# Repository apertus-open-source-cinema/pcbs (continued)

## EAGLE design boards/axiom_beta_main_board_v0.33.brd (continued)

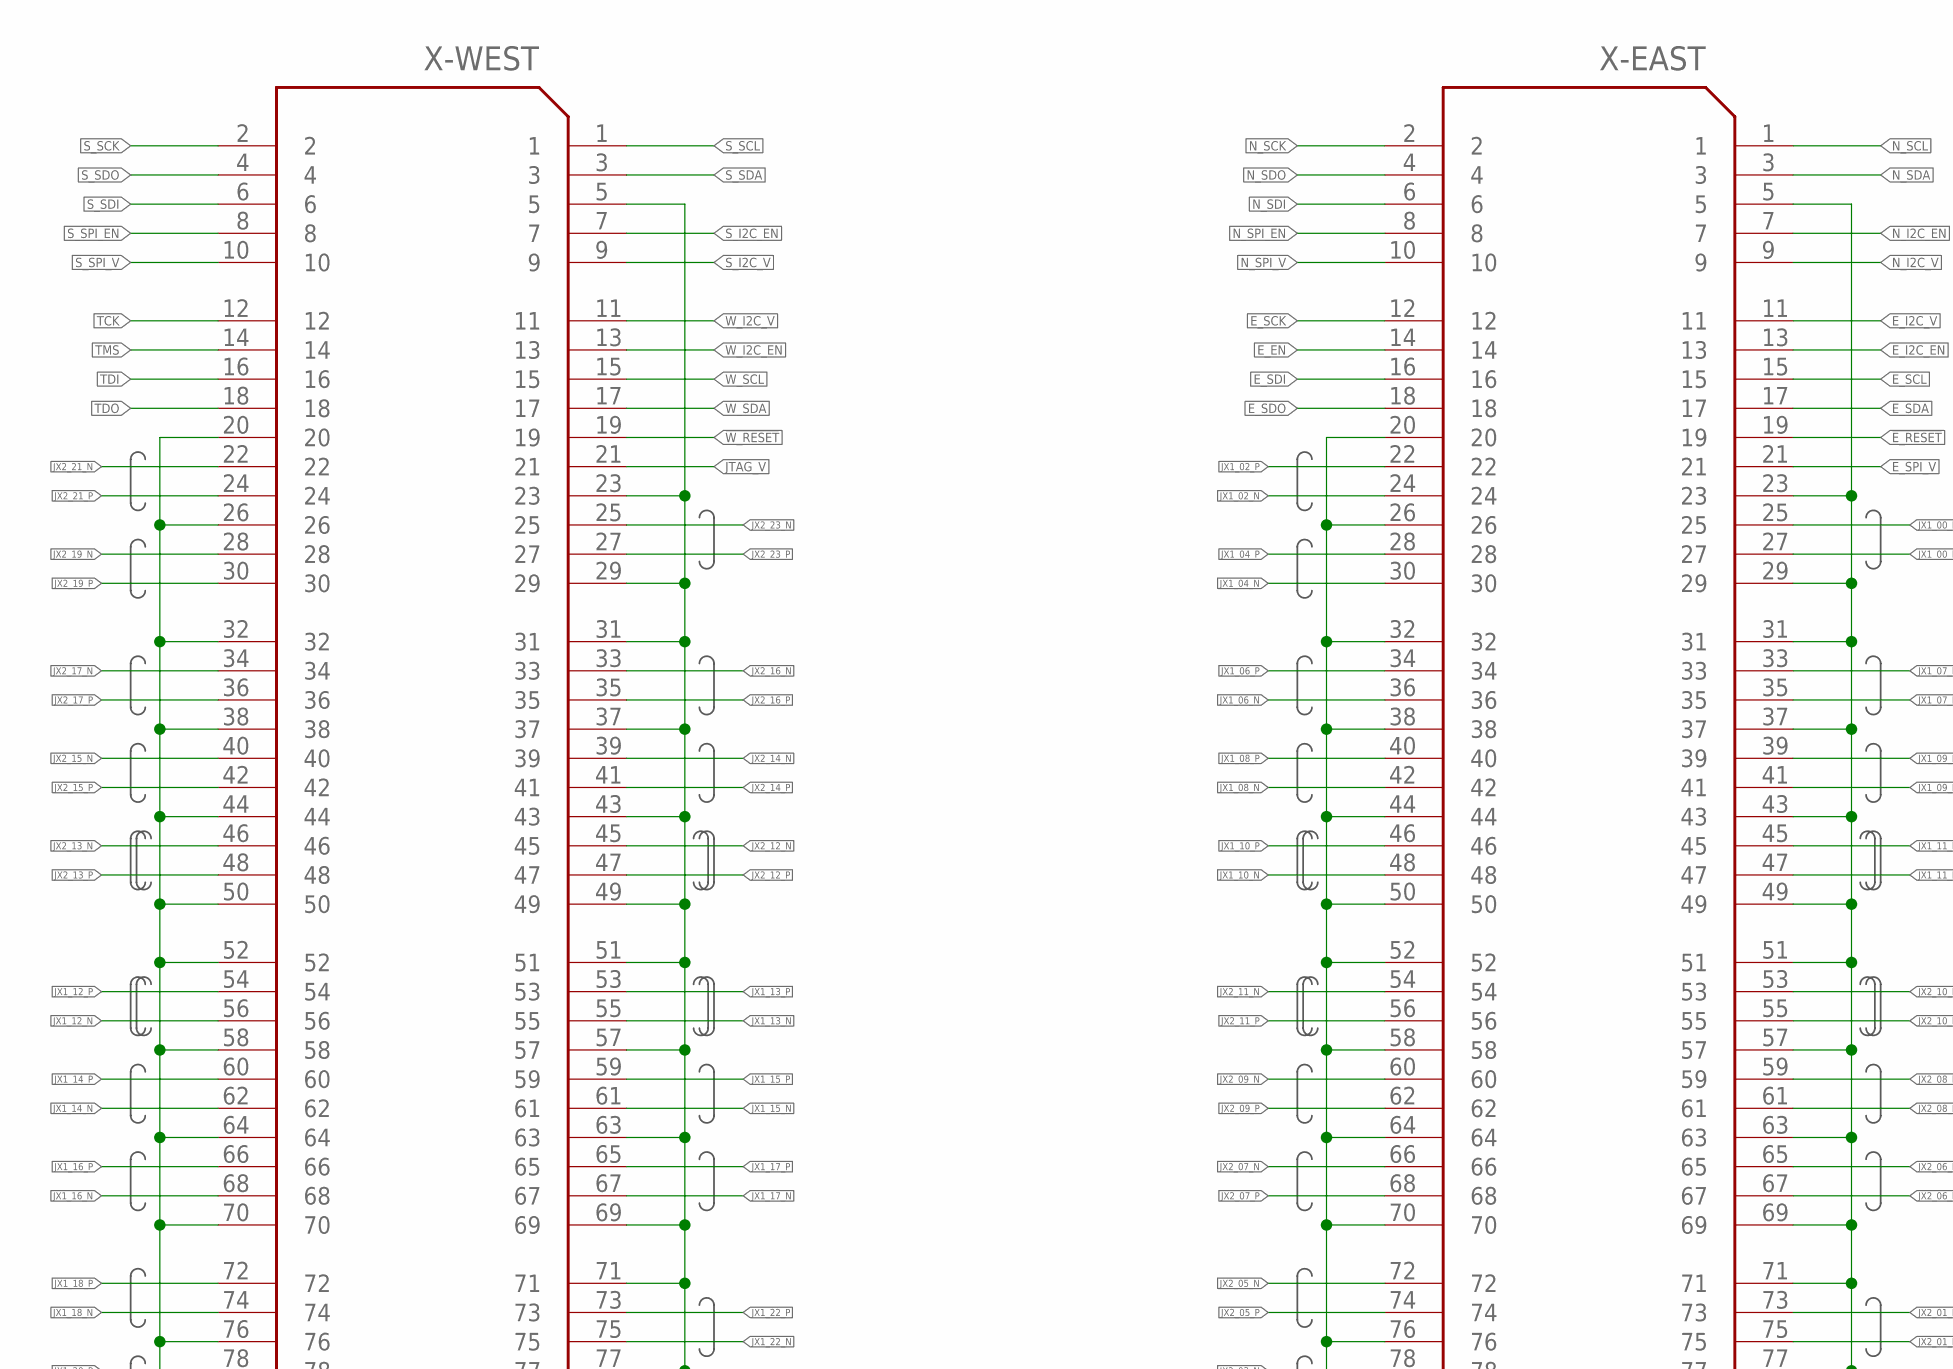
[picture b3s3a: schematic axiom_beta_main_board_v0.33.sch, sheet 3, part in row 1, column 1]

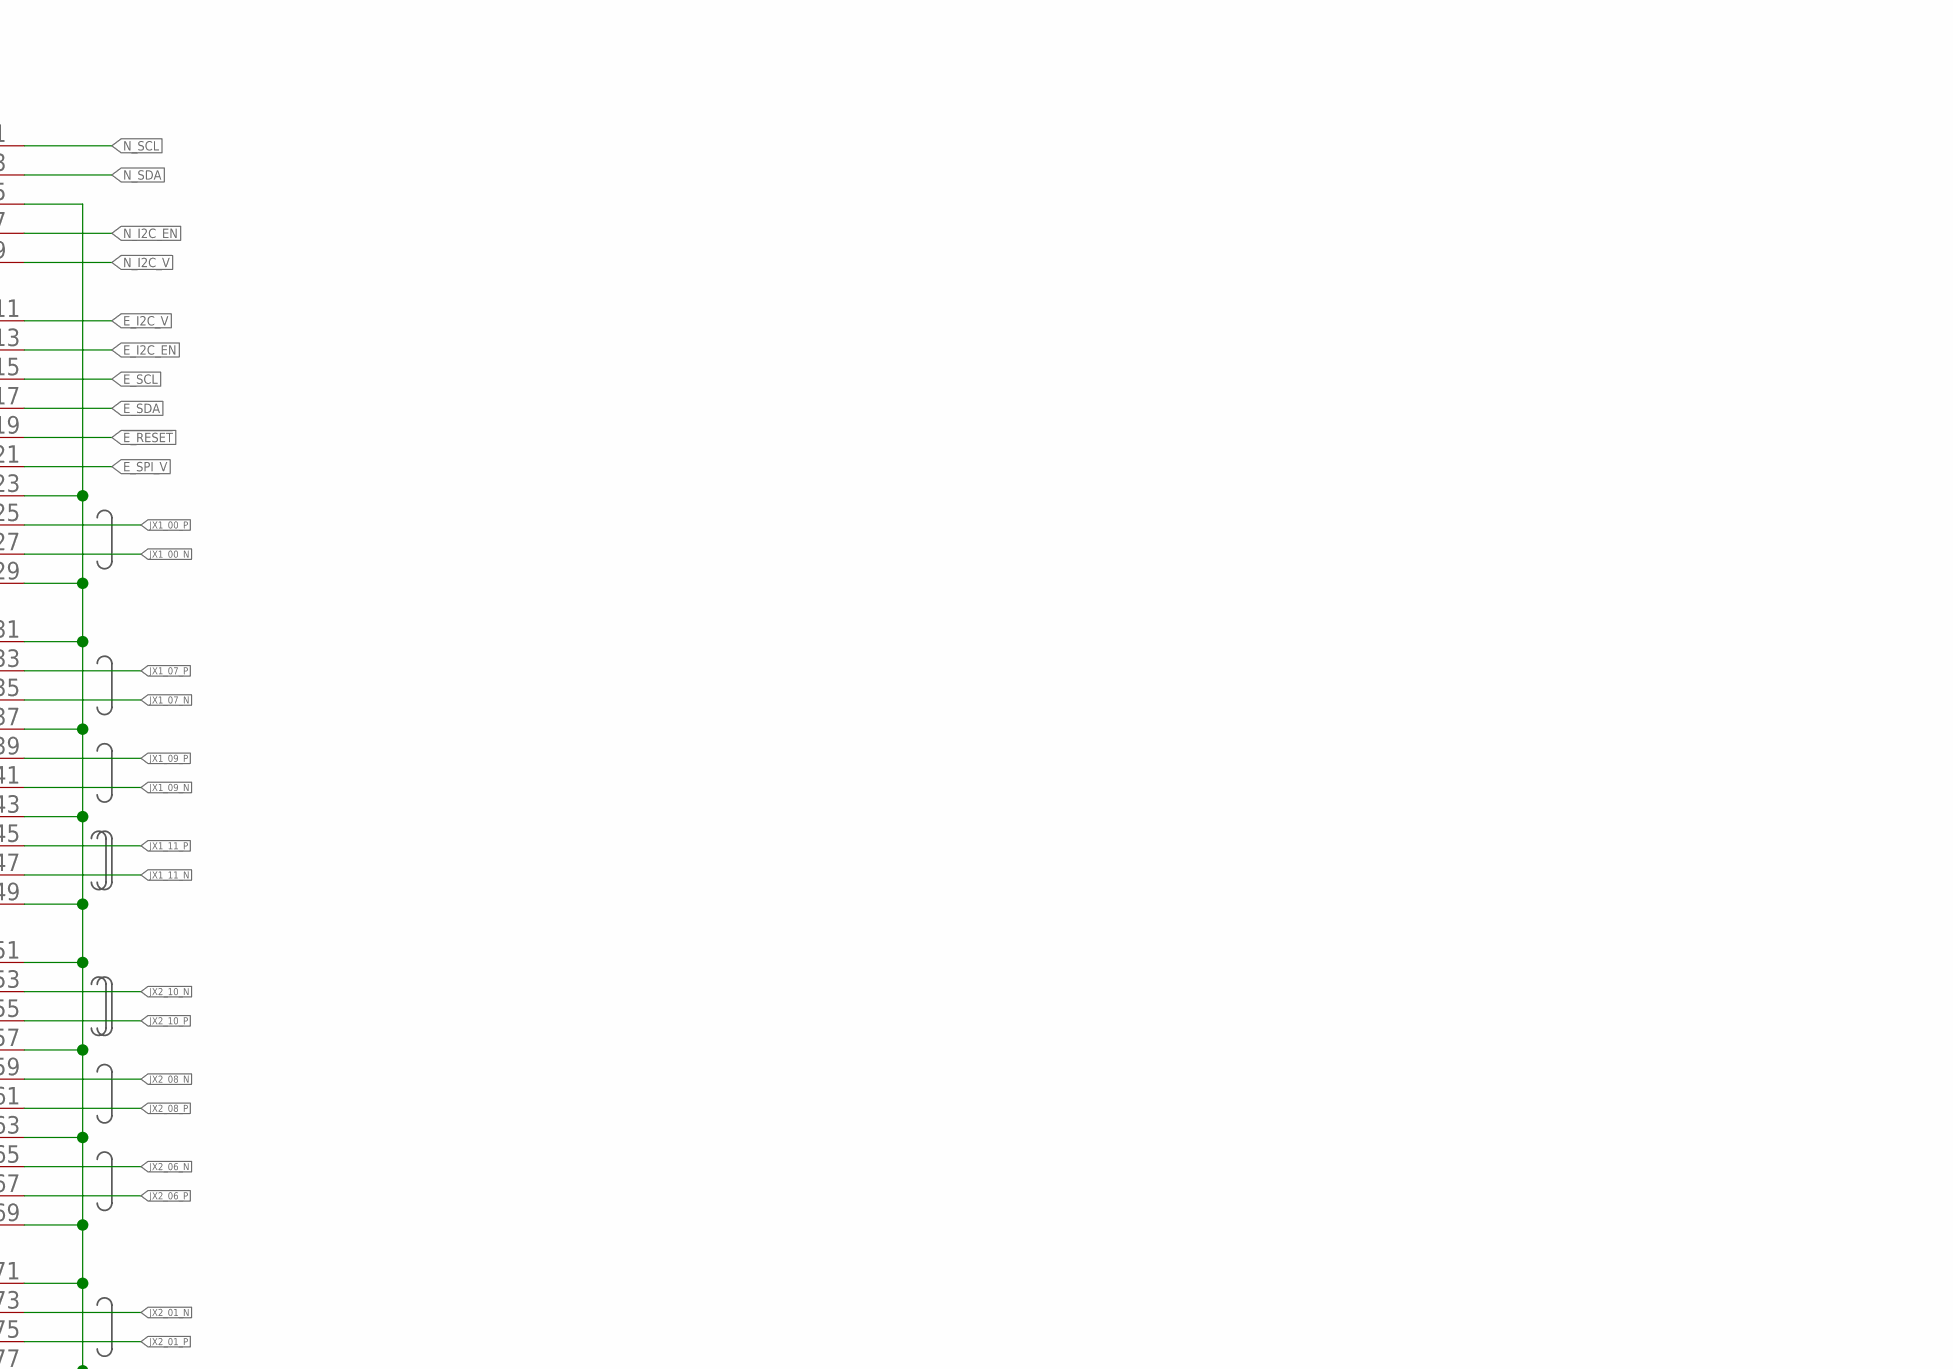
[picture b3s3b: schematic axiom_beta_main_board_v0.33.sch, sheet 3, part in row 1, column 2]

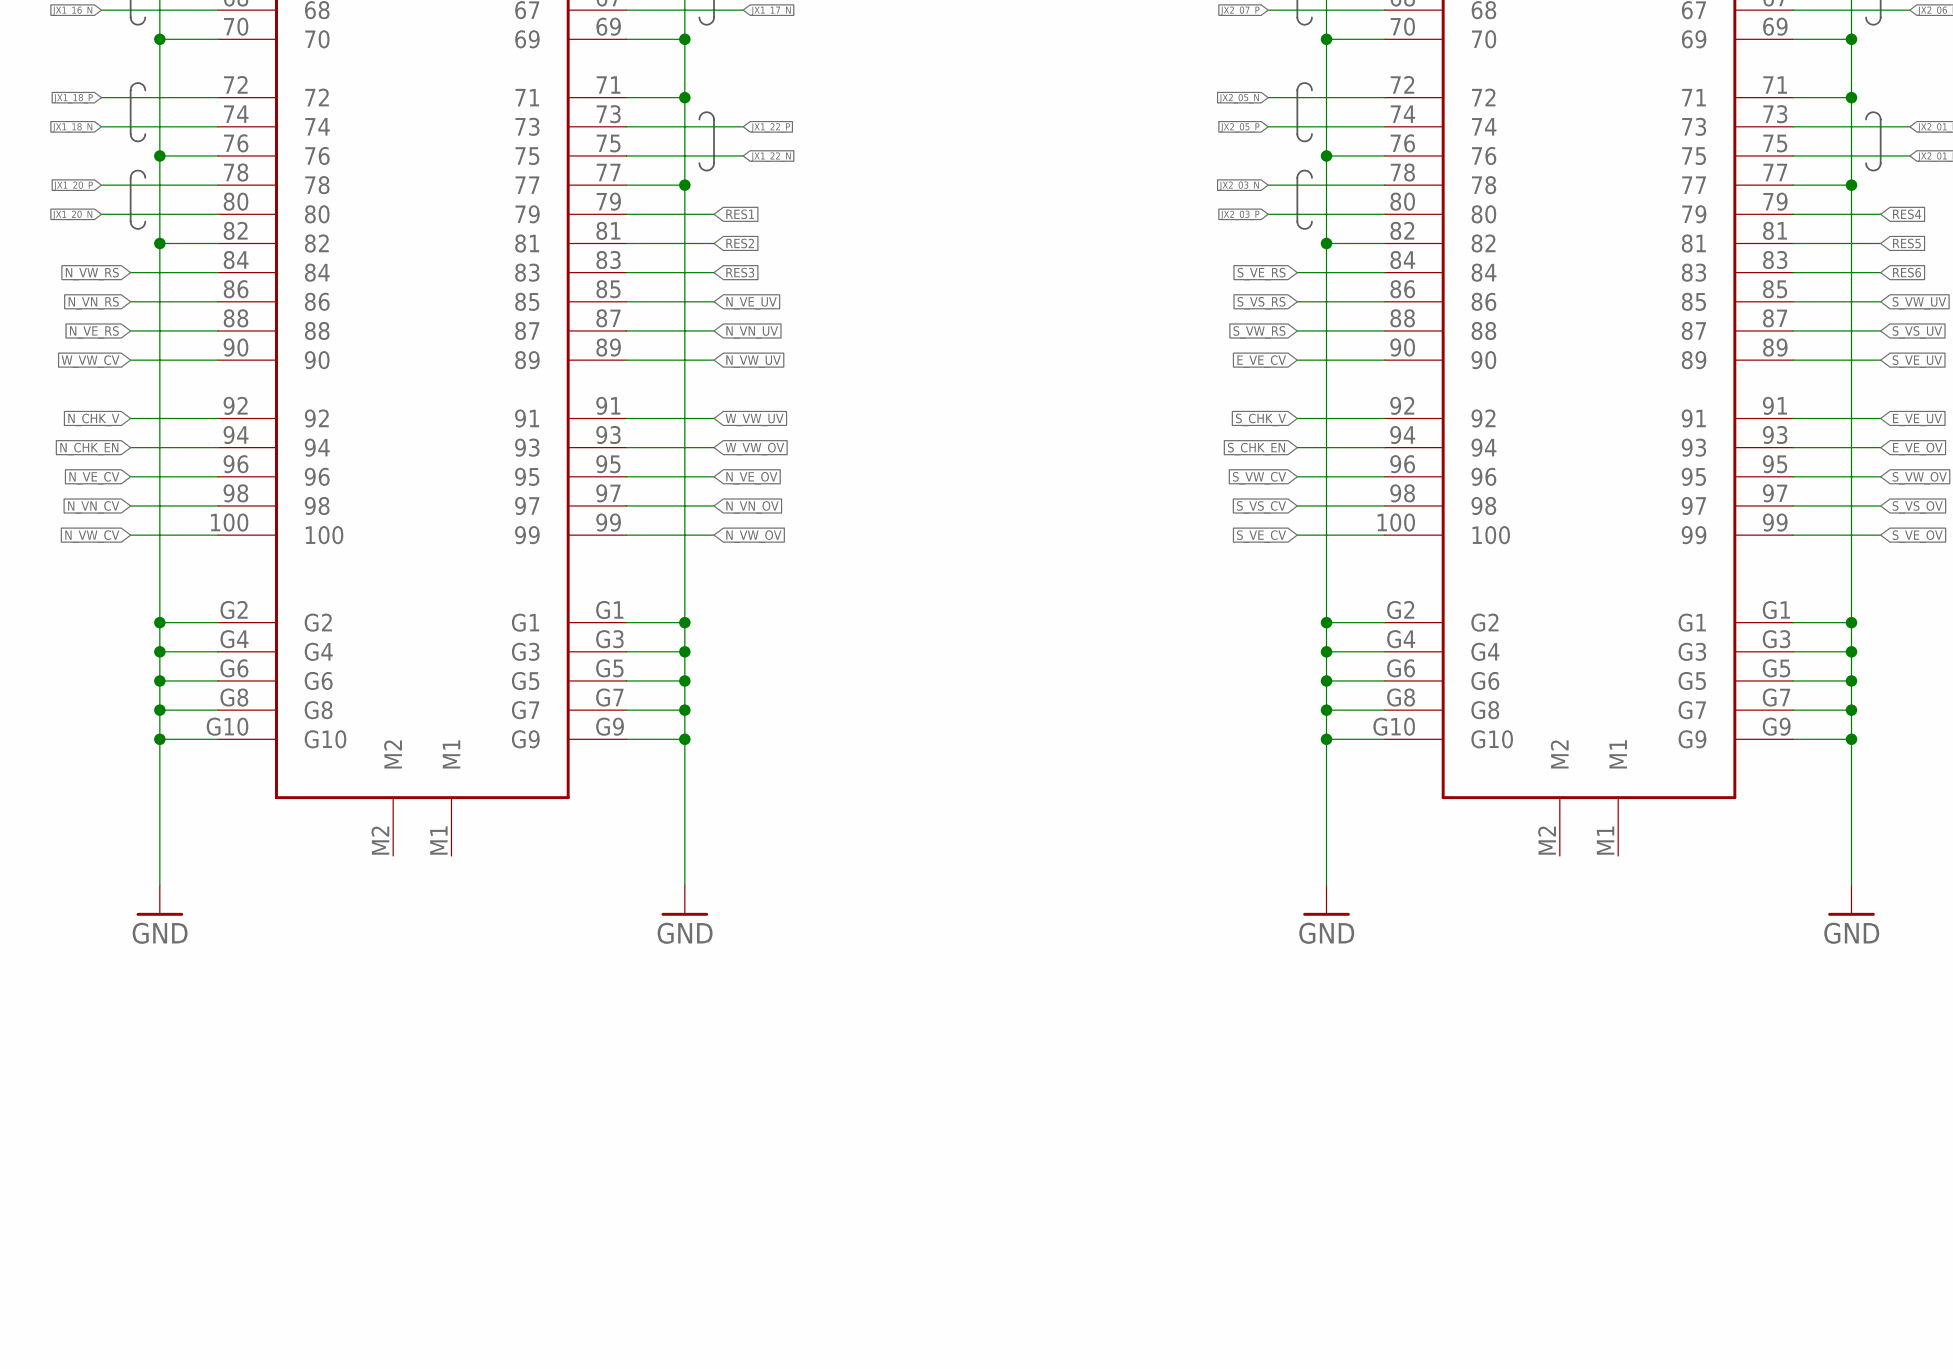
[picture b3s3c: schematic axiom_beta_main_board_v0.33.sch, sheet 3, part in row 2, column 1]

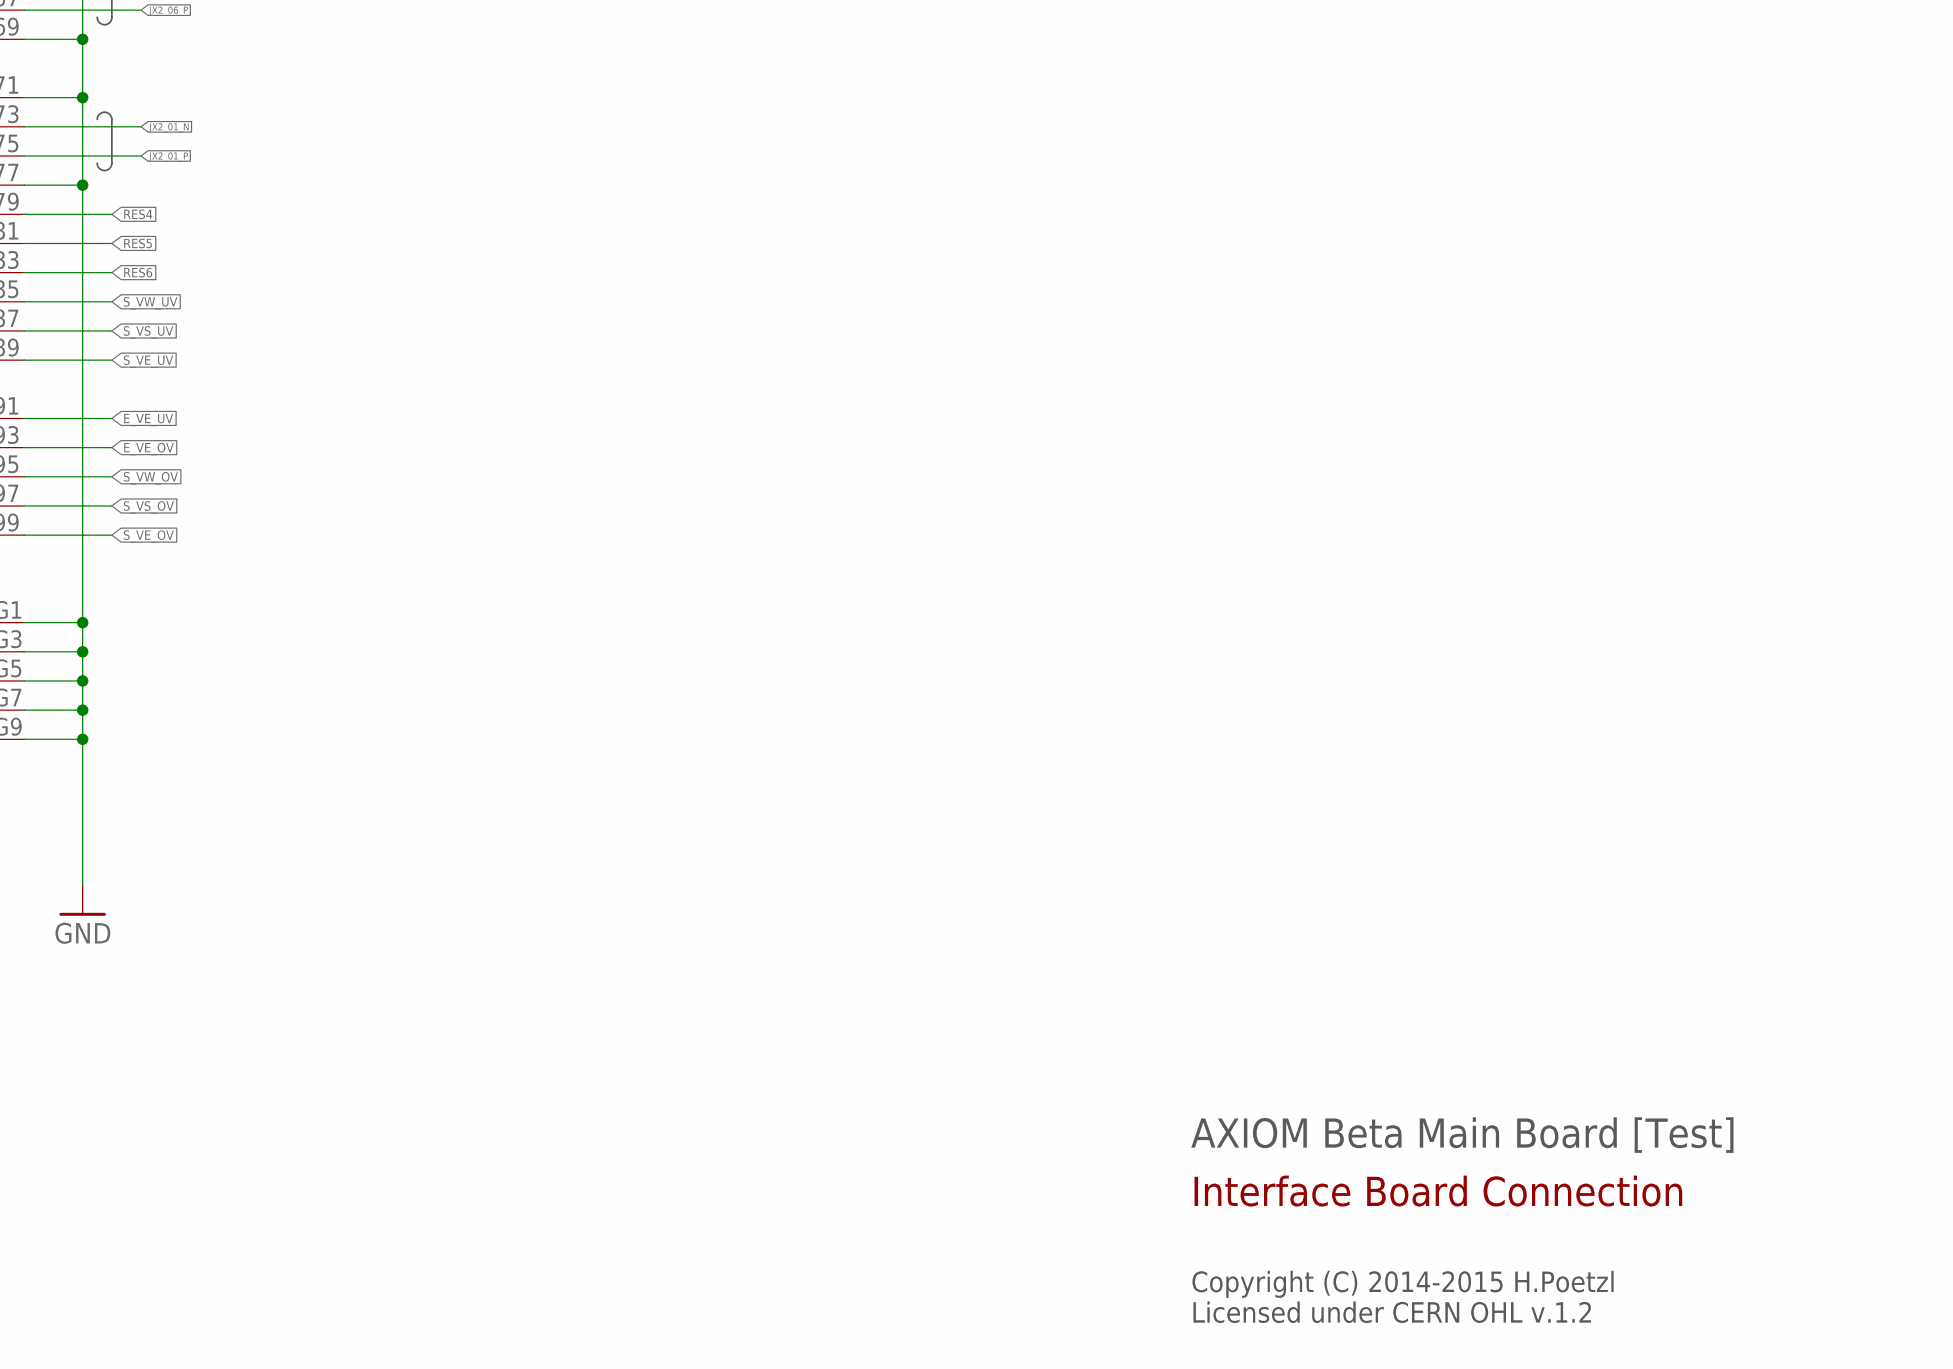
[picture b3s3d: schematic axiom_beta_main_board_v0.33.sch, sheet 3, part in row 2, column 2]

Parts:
X-EAST: FX10-100/10S; FX10A-100S/10
X-WEST: FX10-100/10S; FX10A-100S/10

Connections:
!E_RESET!: X-EAST.19
!W_RESET!: X-WEST.19
E_EN: X-EAST.14; also elsewhere on the board
E_I2C_EN: X-EAST.13
E_I2C_V: X-EAST.11; also elsewhere on the board
E_SCK: X-EAST.12; also elsewhere on the board
E_SCL: X-EAST.15; also elsewhere on the board
E_SDA: X-EAST.17; also elsewhere on the board
E_SDI: X-EAST.16; also elsewhere on the board
E_SDO: X-EAST.18; also elsewhere on the board
E_SPI_V: X-EAST.21; also elsewhere on the board
E_VE_CV: X-EAST.90; also elsewhere on the board
E_VE_OV: X-EAST.93; also elsewhere on the board
E_VE_UV: X-EAST.91; also elsewhere on the board
GND: X-EAST.5, X-EAST.20, X-EAST.23, X-EAST.26, X-EAST.29, X-EAST.31, X-EAST.32, X-EAST.37, X-EAST.38, X-EAST.43, X-EAST.44, X-EAST.49, X-EAST.50, X-EAST.51, X-EAST.52, X-EAST.57, X-EAST.58, X-EAST.63, X-EAST.64, X-EAST.69, X-EAST.70, X-EAST.71, X-EAST.76, X-EAST.77, X-EAST.82, X-EAST.G1, X-EAST.G2, X-EAST.G3, X-EAST.G4, X-EAST.G5, X-EAST.G6, X-EAST.G7, X-EAST.G8, X-EAST.G9, X-EAST.G10, X-WEST.5, X-WEST.20, X-WEST.23, X-WEST.26, X-WEST.29, X-WEST.31, X-WEST.32, X-WEST.37, X-WEST.38, X-WEST.43, X-WEST.44, X-WEST.49, X-WEST.50, X-WEST.51, X-WEST.52, X-WEST.57, X-WEST.58, X-WEST.63, X-WEST.64, X-WEST.69, X-WEST.70, X-WEST.71, X-WEST.76, X-WEST.77, X-WEST.82, X-WEST.G1, X-WEST.G2, X-WEST.G3, X-WEST.G4, X-WEST.G5, X-WEST.G6, X-WEST.G7, X-WEST.G8, X-WEST.G9, X-WEST.G10; also elsewhere on the board
JTAG_V: X-WEST.21; also elsewhere on the board
JX1_00_N: X-EAST.27; also elsewhere on the board
JX1_00_P: X-EAST.25; also elsewhere on the board
JX1_02_N: X-EAST.24; also elsewhere on the board
JX1_02_P: X-EAST.22; also elsewhere on the board
JX1_04_N: X-EAST.30; also elsewhere on the board
JX1_04_P: X-EAST.28; also elsewhere on the board
JX1_06_N: X-EAST.36; also elsewhere on the board
JX1_06_P: X-EAST.34; also elsewhere on the board
JX1_07_N: X-EAST.35; also elsewhere on the board
JX1_07_P: X-EAST.33; also elsewhere on the board
JX1_08_N: X-EAST.42; also elsewhere on the board
JX1_08_P: X-EAST.40; also elsewhere on the board
JX1_09_N: X-EAST.41; also elsewhere on the board
JX1_09_P: X-EAST.39; also elsewhere on the board
JX1_10_N: X-EAST.48; also elsewhere on the board
JX1_10_P: X-EAST.46; also elsewhere on the board
JX1_11_N: X-EAST.47; also elsewhere on the board
JX1_11_P: X-EAST.45; also elsewhere on the board
JX1_12_N: X-WEST.56; also elsewhere on the board
JX1_12_P: X-WEST.54; also elsewhere on the board
JX1_13_N: X-WEST.55; also elsewhere on the board
JX1_13_P: X-WEST.53; also elsewhere on the board
JX1_14_N: X-WEST.62; also elsewhere on the board
JX1_14_P: X-WEST.60; also elsewhere on the board
JX1_15_N: X-WEST.61; also elsewhere on the board
JX1_15_P: X-WEST.59; also elsewhere on the board
JX1_16_N: X-WEST.68; also elsewhere on the board
JX1_16_P: X-WEST.66; also elsewhere on the board
JX1_17_N: X-WEST.67; also elsewhere on the board
JX1_17_P: X-WEST.65; also elsewhere on the board
JX1_18_N: X-WEST.74; also elsewhere on the board
JX1_18_P: X-WEST.72; also elsewhere on the board
JX1_20_N: X-WEST.80; also elsewhere on the board
JX1_20_P: X-WEST.78; also elsewhere on the board
JX1_22_N: X-WEST.75; also elsewhere on the board
JX1_22_P: X-WEST.73; also elsewhere on the board
JX2_01_N: X-EAST.73; also elsewhere on the board
JX2_01_P: X-EAST.75; also elsewhere on the board
JX2_03_N: X-EAST.78; also elsewhere on the board
JX2_03_P: X-EAST.80; also elsewhere on the board
JX2_05_N: X-EAST.72; also elsewhere on the board
JX2_05_P: X-EAST.74; also elsewhere on the board
JX2_06_N: X-EAST.65; also elsewhere on the board
JX2_06_P: X-EAST.67; also elsewhere on the board
JX2_07_N: X-EAST.66; also elsewhere on the board
JX2_07_P: X-EAST.68; also elsewhere on the board
JX2_08_N: X-EAST.59; also elsewhere on the board
JX2_08_P: X-EAST.61; also elsewhere on the board
JX2_09_N: X-EAST.60; also elsewhere on the board
JX2_09_P: X-EAST.62; also elsewhere on the board
JX2_10_N: X-EAST.53; also elsewhere on the board
JX2_10_P: X-EAST.55; also elsewhere on the board
JX2_11_N: X-EAST.54; also elsewhere on the board
JX2_11_P: X-EAST.56; also elsewhere on the board
JX2_12_N: X-WEST.45; also elsewhere on the board
JX2_12_P: X-WEST.47; also elsewhere on the board
JX2_13_N: X-WEST.46; also elsewhere on the board
JX2_13_P: X-WEST.48; also elsewhere on the board
JX2_14_N: X-WEST.39; also elsewhere on the board
JX2_14_P: X-WEST.41; also elsewhere on the board
JX2_15_N: X-WEST.40; also elsewhere on the board
JX2_15_P: X-WEST.42; also elsewhere on the board
JX2_16_N: X-WEST.33; also elsewhere on the board
JX2_16_P: X-WEST.35; also elsewhere on the board
JX2_17_N: X-WEST.34; also elsewhere on the board
JX2_17_P: X-WEST.36; also elsewhere on the board
JX2_19_N: X-WEST.28; also elsewhere on the board
JX2_19_P: X-WEST.30; also elsewhere on the board
JX2_21_N: X-WEST.22; also elsewhere on the board
JX2_21_P: X-WEST.24; also elsewhere on the board
JX2_23_N: X-WEST.25; also elsewhere on the board
JX2_23_P: X-WEST.27; also elsewhere on the board
N_CHK_EN: X-WEST.94
N_CHK_V: X-WEST.92; also elsewhere on the board
N_I2C_EN: X-EAST.7
N_I2C_V: X-EAST.9; also elsewhere on the board
N_SCK: X-EAST.2; also elsewhere on the board
N_SCL: X-EAST.1; also elsewhere on the board
N_SDA: X-EAST.3; also elsewhere on the board
N_SDI: X-EAST.6; also elsewhere on the board
N_SDO: X-EAST.4; also elsewhere on the board
N_SPI_EN: X-EAST.8; also elsewhere on the board
N_SPI_V: X-EAST.10; also elsewhere on the board
N_VE_CV: X-WEST.96; also elsewhere on the board
N_VE_OV: X-WEST.95; also elsewhere on the board
N_VE_RS: X-WEST.88; also elsewhere on the board
N_VE_UV: X-WEST.85; also elsewhere on the board
N_VN_CV: X-WEST.98; also elsewhere on the board
N_VN_OV: X-WEST.97; also elsewhere on the board
N_VN_RS: X-WEST.86; also elsewhere on the board
N_VN_UV: X-WEST.87; also elsewhere on the board
N_VW_CV: X-WEST.100; also elsewhere on the board
N_VW_OV: X-WEST.99; also elsewhere on the board
N_VW_RS: X-WEST.84; also elsewhere on the board
N_VW_UV: X-WEST.89; also elsewhere on the board
RES1: X-WEST.79
RES2: X-WEST.81
RES3: X-WEST.83
RES4: X-EAST.79
RES5: X-EAST.81
RES6: X-EAST.83
S_CHK_EN: X-EAST.94
S_CHK_V: X-EAST.92; also elsewhere on the board
S_I2C_EN: X-WEST.7
S_I2C_V: X-WEST.9; also elsewhere on the board
S_SCK: X-WEST.2; also elsewhere on the board
S_SCL: X-WEST.1; also elsewhere on the board
S_SDA: X-WEST.3; also elsewhere on the board
S_SDI: X-WEST.6; also elsewhere on the board
S_SDO: X-WEST.4; also elsewhere on the board
S_SPI_EN: X-WEST.8; also elsewhere on the board
S_SPI_V: X-WEST.10; also elsewhere on the board
S_VE_CV: X-EAST.100; also elsewhere on the board
S_VE_OV: X-EAST.99; also elsewhere on the board
S_VE_RS: X-EAST.84; also elsewhere on the board
S_VE_UV: X-EAST.89; also elsewhere on the board
S_VS_CV: X-EAST.98; also elsewhere on the board
S_VS_OV: X-EAST.97; also elsewhere on the board
S_VS_RS: X-EAST.86; also elsewhere on the board
S_VS_UV: X-EAST.87; also elsewhere on the board
S_VW_CV: X-EAST.96; also elsewhere on the board
S_VW_OV: X-EAST.95; also elsewhere on the board
S_VW_RS: X-EAST.88; also elsewhere on the board
S_VW_UV: X-EAST.85; also elsewhere on the board
TCK: X-WEST.12; also elsewhere on the board
TDI: X-WEST.16; also elsewhere on the board
TDO: X-WEST.18; also elsewhere on the board
TMS: X-WEST.14; also elsewhere on the board
W_I2C_EN: X-WEST.13
W_I2C_V: X-WEST.11; also elsewhere on the board
W_SCL: X-WEST.15; also elsewhere on the board
W_SDA: X-WEST.17; also elsewhere on the board
W_VW_CV: X-WEST.90; also elsewhere on the board
W_VW_OV: X-WEST.93; also elsewhere on the board
W_VW_UV: X-WEST.91; also elsewhere on the board

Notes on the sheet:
AXIOM Beta Main Board [Test]
Copyright (C) 2014-2015 H.Poetzl Licensed under CERN OHL v.1.2
Interface Board Connection
